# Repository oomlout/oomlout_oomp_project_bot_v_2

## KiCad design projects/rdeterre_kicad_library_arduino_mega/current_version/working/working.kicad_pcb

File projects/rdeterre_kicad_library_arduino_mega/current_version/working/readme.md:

# kicad_library
 
## summary 
* id: rdeterre_kicad_library_arduino_mega
* user: rdeterre
* name: kicad_library
* board: arduino_mega
* repo: https://github.com/rdeterre/kicad-library
* src_file_repo_kicad_pcb: template/Arduino_Mega_R3/Arduino_Mega.kicad_pcb
* src_file_repo_kicad_pcb_link: https://github.com/rdeterre/kicad-library/tree/master/template/Arduino_Mega_R3/Arduino_Mega.kicad_pcb

* src_file_repo_sch: template/Arduino_Mega_R3/Arduino_Mega.sch
* src_file_repo_sch_link: https://github.com/rdeterre/kicad-library/tree/master/template/Arduino_Mega_R3/Arduino_Mega.sch
* full details link: https://github.com/oomlout/oomlout_oomp_project_bot_v_2/tree/main/projects/rdeterre_kicad_library_arduino_mega/current_version/working

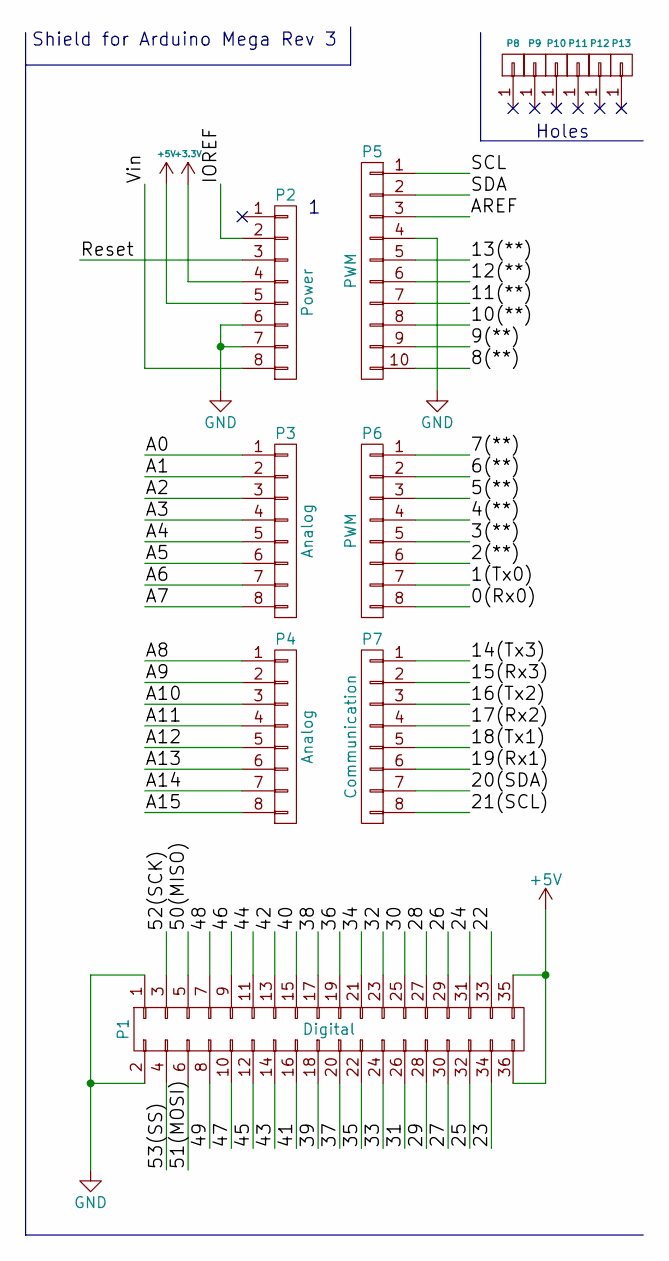
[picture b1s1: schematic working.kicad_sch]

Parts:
P1: Digital; Socket_Strip_Arduino_2x18
P2: Power; Socket_Strip_Arduino_1x08
P3, P4: Analog; Socket_Strip_Arduino_1x08
P5: PWM; Socket_Strip_Arduino_1x10
P6: PWM; Socket_Strip_Arduino_1x08
P7: Communication; Socket_Strip_Arduino_1x08
P8, P9, P10, P11, P12, P13: CONN_01X01; Arduino_1pin

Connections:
+3V3: P2.4
+5V: P1.35, P1.36, P2.5
/0(Rx0): P6.8
/1(Tx0): P6.7
/2(**): P6.6
/3(**): P6.5
/4(**): P6.4
/5(**): P6.3
/6(**): P6.2
/7(**): P6.1
/8(**): P5.10
/9(**): P5.9
/10(**): P5.8
/11(**): P5.7
/12(**): P5.6
/13(**): P5.5
/14(Tx3): P7.1
/15(Rx3): P7.2
/16(Tx2): P7.3
/17(Rx2): P7.4
/18(Tx1): P7.5
/19(Rx1): P7.6
/20(SDA): P7.7
/21(SCL): P7.8
/22: P1.33
/23: P1.34
/24: P1.31
/25: P1.32
/26: P1.29
/27: P1.30
/28: P1.27
/29: P1.28
/30: P1.25
/31: P1.26
/32: P1.23
/33: P1.24
/34: P1.21
/35: P1.22
/36: P1.19
/37: P1.20
/38: P1.17
/39: P1.18
/40: P1.15
/41: P1.16
/42: P1.13
/43: P1.14
/44: P1.11
/45: P1.12
/46: P1.9
/47: P1.10
/48: P1.7
/49: P1.8
/50(MISO): P1.5
/51(MOSI): P1.6
/52(SCK): P1.3
/53(SS): P1.4
/A0: P3.1
/A1: P3.2
/A2: P3.3
/A3: P3.4
/A4: P3.5
/A5: P3.6
/A6: P3.7
/A7: P3.8
/A8: P4.1
/A9: P4.2
/A10: P4.3
/A11: P4.4
/A12: P4.5
/A13: P4.6
/A14: P4.7
/A15: P4.8
/AREF: P5.3
/IOREF: P2.2
/Reset: P2.3
/SCL: P5.1
/SDA: P5.2
/Vin: P2.8
GND: P1.1, P1.2, P2.6, P2.7, P5.4

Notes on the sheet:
Holes
Shield for Arduino Mega Rev 3

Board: 2 copper layers, 13 parts (0 on the bottom side), 2 nets, no tracks yet.

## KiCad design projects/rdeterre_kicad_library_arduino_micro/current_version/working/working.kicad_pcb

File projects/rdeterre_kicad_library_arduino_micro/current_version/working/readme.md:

# kicad_library
 
## summary 
* id: rdeterre_kicad_library_arduino_micro
* user: rdeterre
* name: kicad_library
* board: arduino_micro
* repo: https://github.com/rdeterre/kicad-library
* src_file_repo_kicad_pcb: template/Arduino_Micro/Arduino_Micro.kicad_pcb
* src_file_repo_kicad_pcb_link: https://github.com/rdeterre/kicad-library/tree/master/template/Arduino_Micro/Arduino_Micro.kicad_pcb

* src_file_repo_sch: template/Arduino_Micro/Arduino_Micro.sch
* src_file_repo_sch_link: https://github.com/rdeterre/kicad-library/tree/master/template/Arduino_Micro/Arduino_Micro.sch
* full details link: https://github.com/oomlout/oomlout_oomp_project_bot_v_2/tree/main/projects/rdeterre_kicad_library_arduino_micro/current_version/working

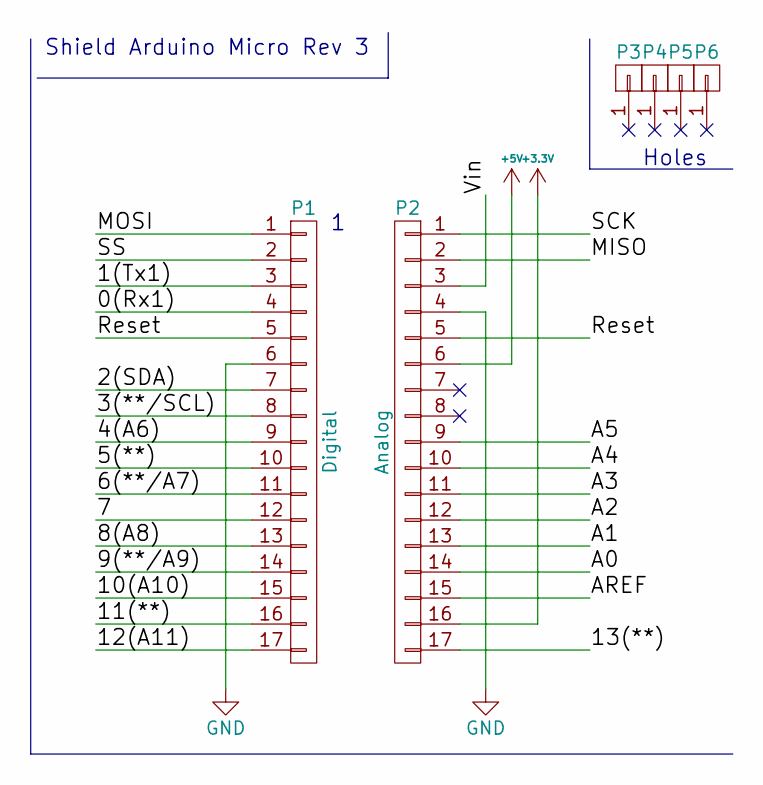
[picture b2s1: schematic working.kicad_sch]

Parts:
P1: Digital; Socket_Strip_Arduino_1x17
P2: Analog; Socket_Strip_Arduino_1x17
P3, P4, P5, P6: CONN_01X01; 1pin_Micro

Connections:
+3V3: P2.16
+5V: P2.6
/0(Rx1): P1.4
/1(Tx1): P1.3
/2(SDA): P1.7
/3(**/SCL): P1.8
/4(A6): P1.9
/5(**): P1.10
/6(**/A7): P1.11
/7: P1.12
/8(A8): P1.13
/9(**/A9): P1.14
/10(A10): P1.15
/11(**): P1.16
/12(A11): P1.17
/13(**): P2.17
/A0: P2.14
/A1: P2.13
/A2: P2.12
/A3: P2.11
/A4: P2.10
/A5: P2.9
/AREF: P2.15
/MISO: P2.2
/MOSI: P1.1
/Reset: P1.5, P2.5
/SCK: P2.1
/SS: P1.2
/Vin: P2.3
GND: P1.6, P2.4

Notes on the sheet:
Holes
Shield Arduino Micro Rev 3

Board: 2 copper layers, 6 parts (0 on the bottom side), 2 nets, no tracks yet.

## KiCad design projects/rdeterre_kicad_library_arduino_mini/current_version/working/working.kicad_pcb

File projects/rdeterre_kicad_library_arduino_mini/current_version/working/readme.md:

# kicad_library
 
## summary 
* id: rdeterre_kicad_library_arduino_mini
* user: rdeterre
* name: kicad_library
* board: arduino_mini
* repo: https://github.com/rdeterre/kicad-library
* src_file_repo_kicad_pcb: template/Arduino_Mini/Arduino_Mini.kicad_pcb
* src_file_repo_kicad_pcb_link: https://github.com/rdeterre/kicad-library/tree/master/template/Arduino_Mini/Arduino_Mini.kicad_pcb

* src_file_repo_sch: template/Arduino_Mini/Arduino_Mini.sch
* src_file_repo_sch_link: https://github.com/rdeterre/kicad-library/tree/master/template/Arduino_Mini/Arduino_Mini.sch
* full details link: https://github.com/oomlout/oomlout_oomp_project_bot_v_2/tree/main/projects/rdeterre_kicad_library_arduino_mini/current_version/working

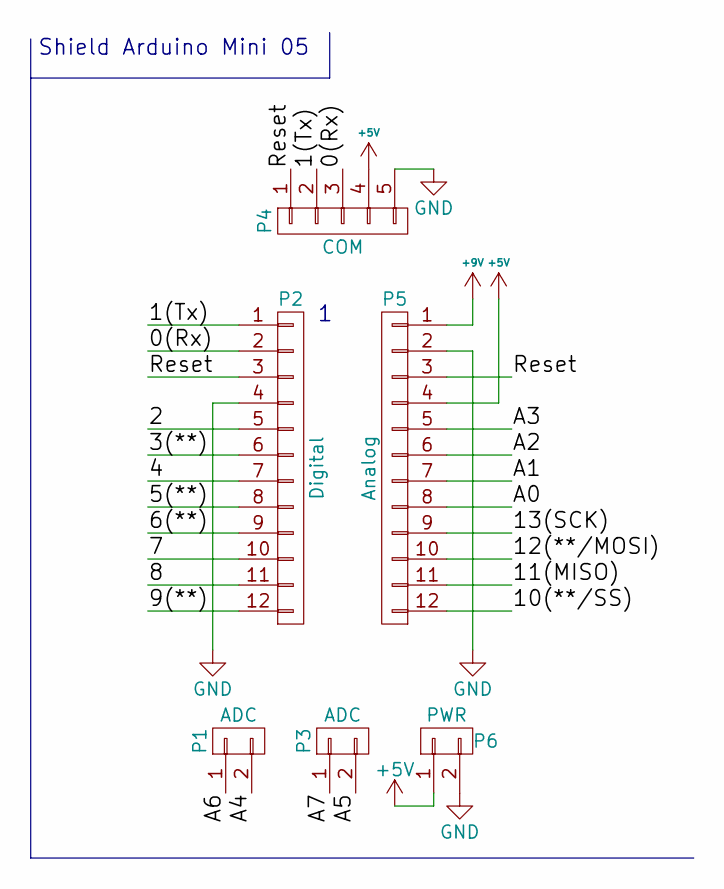
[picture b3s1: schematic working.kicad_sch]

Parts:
P1, P3: ADC; Socket_Strip_Arduino_1x02
P2: Digital; Socket_Strip_Arduino_1x12
P4: COM; Socket_Strip_Arduino_1x05
P5: Analog; Socket_Strip_Arduino_1x12
P6: PWR; Socket_Strip_Arduino_1x02

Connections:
+5V: P4.4, P5.4, P6.1
+9V: P5.1
/0(Rx): P2.2, P4.3
/1(Tx): P2.1, P4.2
/2: P2.5
/3(**): P2.6
/4: P2.7
/5(**): P2.8
/6(**): P2.9
/7: P2.10
/8: P2.11
/9(**): P2.12
/10(**/SS): P5.12
/11(MISO): P5.11
/12(**/MOSI): P5.10
/13(SCK): P5.9
/A0: P5.8
/A1: P5.7
/A2: P5.6
/A3: P5.5
/A4: P1.2
/A5: P3.2
/A6: P1.1
/A7: P3.1
/Reset: P2.3, P4.1, P5.3
GND: P2.4, P4.5, P5.2, P6.2

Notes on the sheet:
Shield Arduino Mini 05

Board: 2 copper layers, 6 parts (0 on the bottom side), 5 nets, no tracks yet.

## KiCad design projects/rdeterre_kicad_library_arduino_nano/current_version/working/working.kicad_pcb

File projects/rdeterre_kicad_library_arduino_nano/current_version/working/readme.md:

# kicad_library
 
## summary 
* id: rdeterre_kicad_library_arduino_nano
* user: rdeterre
* name: kicad_library
* board: arduino_nano
* repo: https://github.com/rdeterre/kicad-library
* src_file_repo_kicad_pcb: template/Arduino_Nano/Arduino_Nano.kicad_pcb
* src_file_repo_kicad_pcb_link: https://github.com/rdeterre/kicad-library/tree/master/template/Arduino_Nano/Arduino_Nano.kicad_pcb

* src_file_repo_sch: template/Arduino_Nano/Arduino_Nano.sch
* src_file_repo_sch_link: https://github.com/rdeterre/kicad-library/tree/master/template/Arduino_Nano/Arduino_Nano.sch
* full details link: https://github.com/oomlout/oomlout_oomp_project_bot_v_2/tree/main/projects/rdeterre_kicad_library_arduino_nano/current_version/working

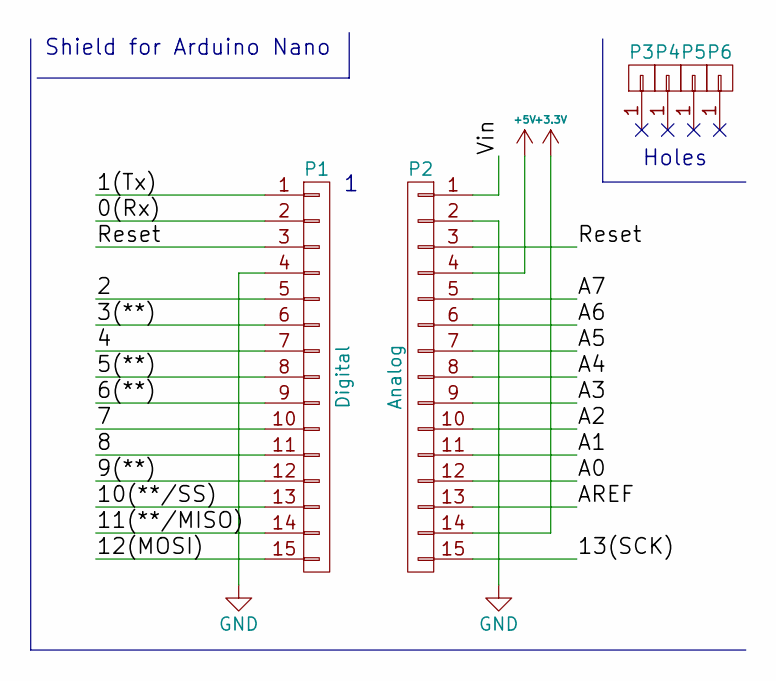
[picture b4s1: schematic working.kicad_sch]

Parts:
P1: Digital; Socket_Strip_Arduino_1x15
P2: Analog; Socket_Strip_Arduino_1x15
P3, P4, P5, P6: CONN_01X01; 1pin_Nano

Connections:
+3V3: P2.14
+5V: P2.4
/0(Rx): P1.2
/1(Tx): P1.1
/2: P1.5
/3(**): P1.6
/4: P1.7
/5(**): P1.8
/6(**): P1.9
/7: P1.10
/8: P1.11
/9(**): P1.12
/10(**/SS): P1.13
/11(**/MISO): P1.14
/12(MOSI): P1.15
/13(SCK): P2.15
/A0: P2.12
/A1: P2.11
/A2: P2.10
/A3: P2.9
/A4: P2.8
/A5: P2.7
/A6: P2.6
/A7: P2.5
/AREF: P2.13
/Reset: P1.3, P2.3
/Vin: P2.1
GND: P1.4, P2.2

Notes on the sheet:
Shield for Arduino Nano
Holes

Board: 2 copper layers, 6 parts (0 on the bottom side), 2 nets, no tracks yet.

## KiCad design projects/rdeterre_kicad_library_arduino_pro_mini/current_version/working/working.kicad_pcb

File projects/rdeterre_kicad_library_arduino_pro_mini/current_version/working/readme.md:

# kicad_library
 
## summary 
* id: rdeterre_kicad_library_arduino_pro_mini
* user: rdeterre
* name: kicad_library
* board: arduino_pro_mini
* repo: https://github.com/rdeterre/kicad-library
* src_file_repo_kicad_pcb: template/Arduino_Pro_Mini/Arduino_Pro_Mini.kicad_pcb
* src_file_repo_kicad_pcb_link: https://github.com/rdeterre/kicad-library/tree/master/template/Arduino_Pro_Mini/Arduino_Pro_Mini.kicad_pcb

* src_file_repo_sch: template/Arduino_Pro_Mini/Arduino_Pro_Mini.sch
* src_file_repo_sch_link: https://github.com/rdeterre/kicad-library/tree/master/template/Arduino_Pro_Mini/Arduino_Pro_Mini.sch
* full details link: https://github.com/oomlout/oomlout_oomp_project_bot_v_2/tree/main/projects/rdeterre_kicad_library_arduino_pro_mini/current_version/working

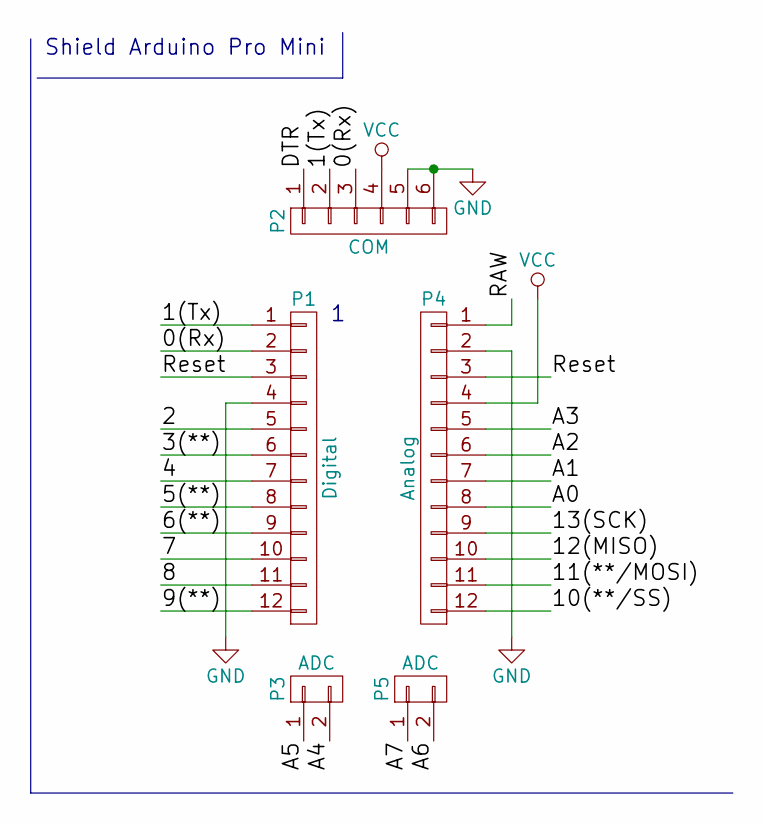
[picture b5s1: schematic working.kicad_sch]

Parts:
P1: Digital; Socket_Strip_Arduino_1x12
P2: COM; Socket_Strip_Arduino_1x06
P3, P5: ADC; Socket_Strip_Arduino_1x02
P4: Analog; Socket_Strip_Arduino_1x12

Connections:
/0(Rx): P1.2, P2.3
/1(Tx): P1.1, P2.2
/2: P1.5
/3(**): P1.6
/4: P1.7
/5(**): P1.8
/6(**): P1.9
/7: P1.10
/8: P1.11
/9(**): P1.12
/10(**/SS): P4.12
/11(**/MOSI): P4.11
/12(MISO): P4.10
/13(SCK): P4.9
/A0: P4.8
/A1: P4.7
/A2: P4.6
/A3: P4.5
/A4: P3.2
/A5: P3.1
/A6: P5.2
/A7: P5.1
/DTR: P2.1
/RAW: P4.1
/Reset: P1.3, P4.3
GND: P1.4, P2.5, P2.6, P4.2
VCC: P2.4, P4.4

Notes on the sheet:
Shield Arduino Pro Mini

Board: 2 copper layers, 5 parts (0 on the bottom side), 5 nets, no tracks yet.
